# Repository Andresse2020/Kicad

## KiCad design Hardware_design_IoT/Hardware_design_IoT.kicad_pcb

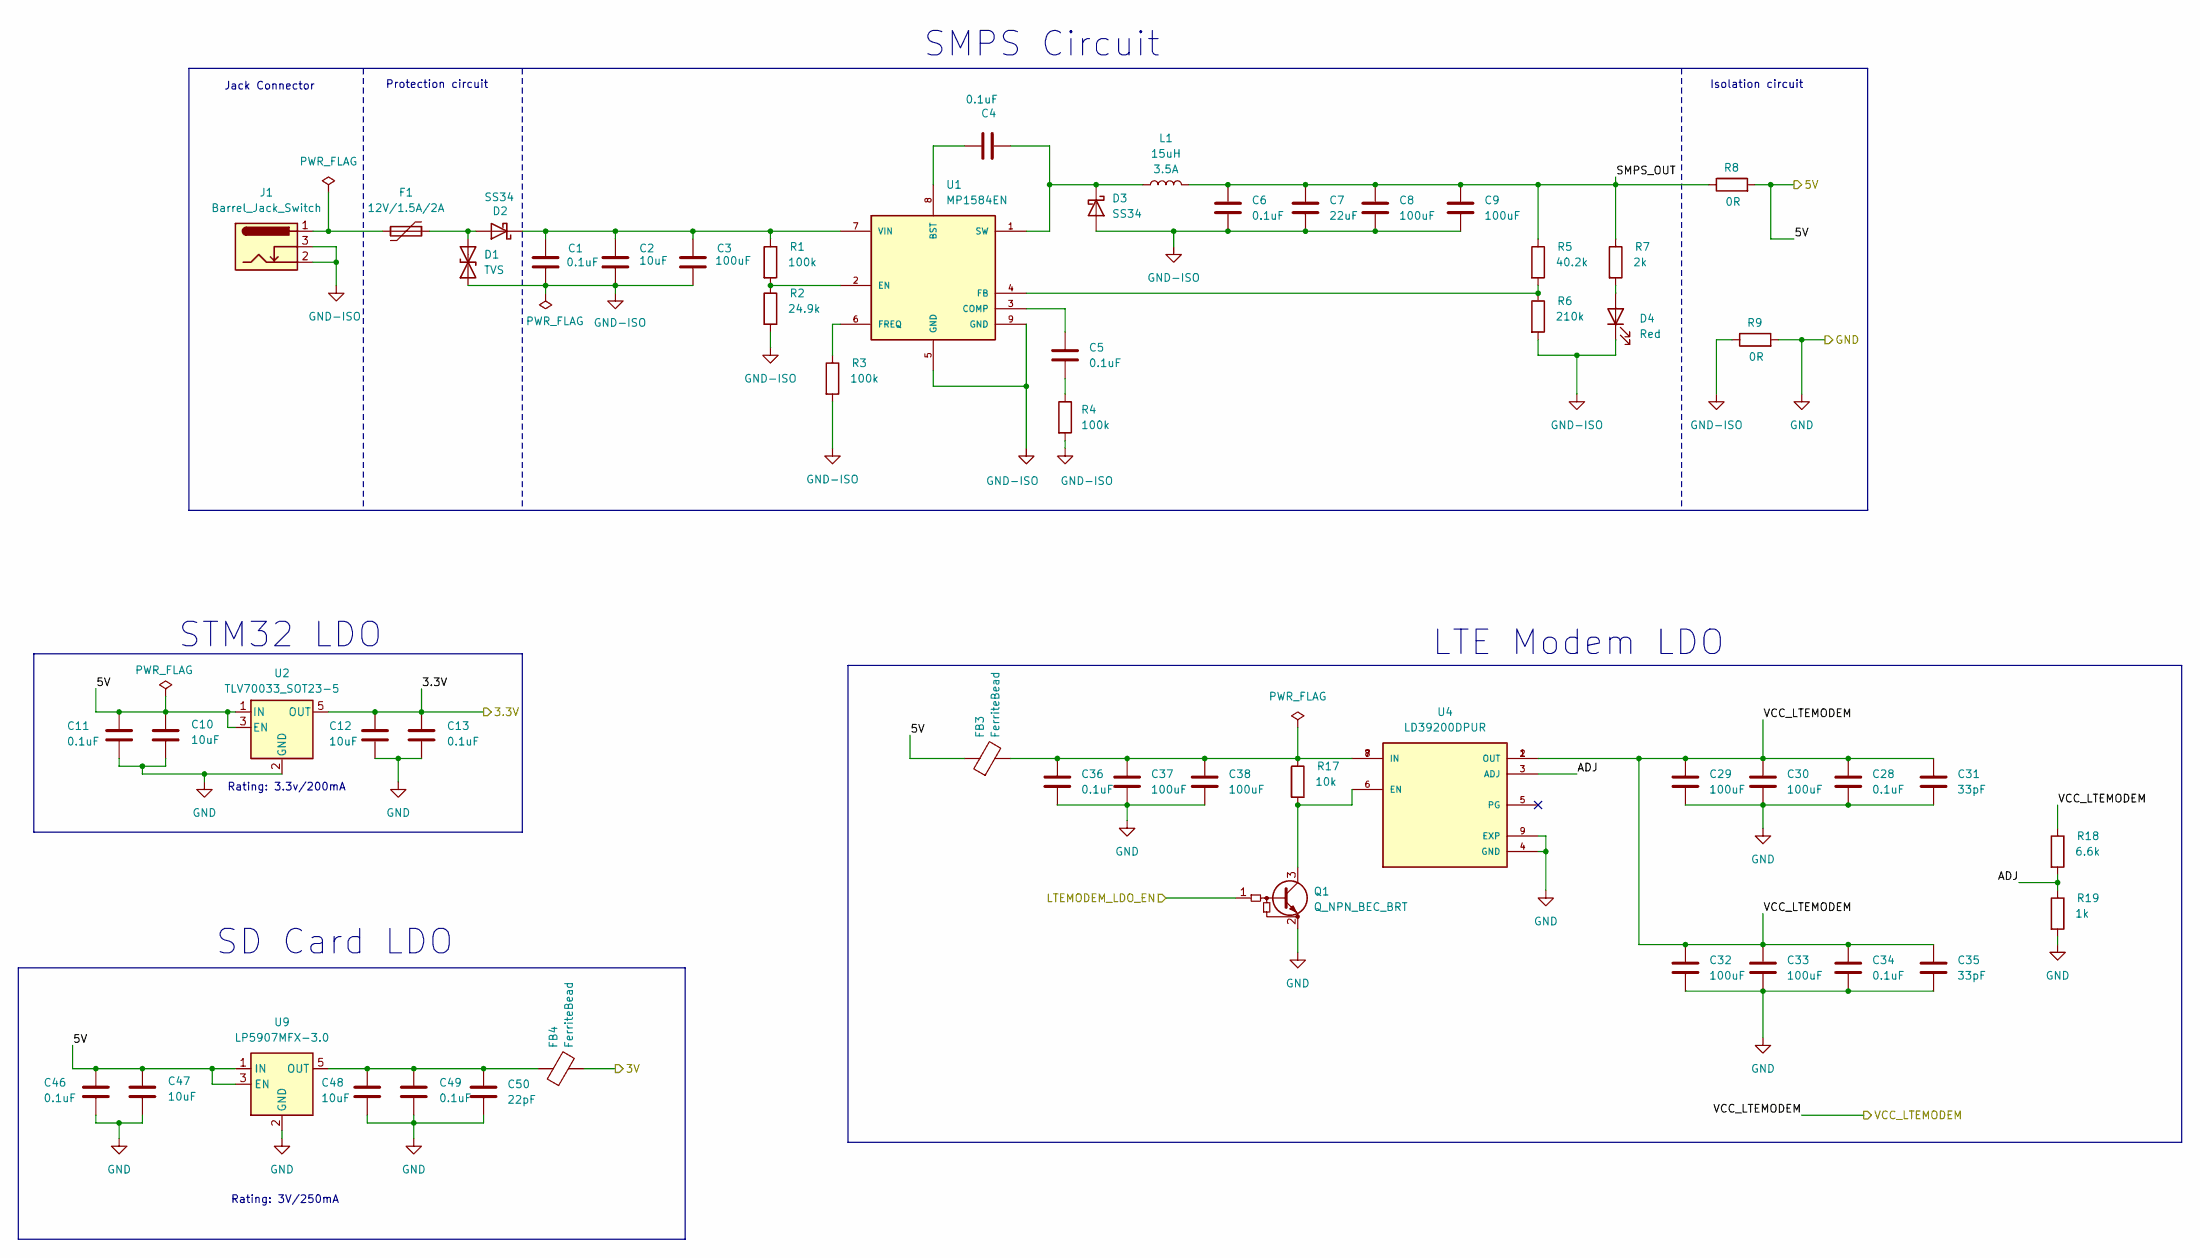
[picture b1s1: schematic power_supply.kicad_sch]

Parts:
C1, C4, C5, C6, C28, C34, C36: 0.1uF; C_0603_1608Metric_Pad1.08x0.95mm_HandSolder
C2: 10uF; C_0603_1608Metric_Pad1.08x0.95mm_HandSolder
C3, C8, C9, C29, C30, C32, C33, C37, C38: 100uF; C_1206_3216Metric_Pad1.33x1.80mm_HandSolder
C7: 22uF; C_0603_1608Metric_Pad1.08x0.95mm_HandSolder
C10, C12, C47, C48: 10uF; C_0603_1608Metric_Pad1.08x0.95mm_HandSolder; Voltage 1kV; Tolerance 100%
C11, C13, C46, C49: 0.1uF; C_0603_1608Metric_Pad1.08x0.95mm_HandSolder; Voltage 1kV; Tolerance 100%
C31, C35: 33pF; C_0603_1608Metric_Pad1.08x0.95mm_HandSolder
C50: 22pF; C_0603_1608Metric_Pad1.08x0.95mm_HandSolder
D1: TVS; D_0805_2012Metric_Pad1.15x1.40mm_HandSolder
D2, D3: SS34; D_SMA
D4: Red; LED_0402_1005Metric
F1: 12V/1.5A/2A; Fuse_0805_2012Metric
FB3, FB4: FerriteBead; BEADC2012X105N
J1: Barrel_Jack_Switch; BarrelJack_CLIFF_FC681465S_SMT_Horizontal
L1: 15uH; L_6.3x6.3_H3
Q1: Q_NPN_BEC_BRT; SOT-23
R1, R3, R4: 100k; R_0603_1608Metric
R2: 24.9k; R_0603_1608Metric
R5: 40.2k; R_0603_1608Metric
R6: 210k; R_0603_1608Metric
R7: 2k; R_0603_1608Metric
R8, R9: 0R; R_0603_1608Metric
R17: 10k; R_0603_1608Metric
R18: 6.6k; R_0603_1608Metric
R19: 1k; R_0603_1608Metric
U1: MP1584EN; SOIC127P600X170-9N
U2: TLV70033_SOT23-5; SOT-23-5
U4: LD39200DPUR; SON80P400X400X100-9N; PARTREV 3
U9: LP5907MFX-3.0; SOT-23-5

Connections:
/3.3V: C12.1, C13.1, U2.5 (OUT); also elsewhere on the board
/3V: FB4.2; also elsewhere on the board
/LTEMODEM_LDO_EN: Q1.1 (B); also elsewhere on the board
/Power Supply/5V: C10.1, C11.1, C46.1, C47.1, FB3.1, R8.2, U2.1 (IN), U2.3 (EN), U9.1 (IN), U9.3 (EN)
/Power Supply/ADJ: R18.2, R19.1, U4.3 (ADJ)
/Power Supply/SMPS_OUT: C6.1, C7.1, C8.1, C9.1, L1.2, R5.1, R7.1, R8.1
/VCC_LTEMODEM: C28.1, C29.1, C30.1, C31.1, C32.1, C33.1, C34.1, C35.1, R18.1, U4.1 (OUT), U4.2 (OUT); also elsewhere on the board
GND: C10.2, C11.2, C12.2, C13.2, C28.2, C29.2, C30.2, C31.2, C32.2, C33.2, C34.2, C35.2, C36.2, C37.2, C38.2, C46.2, C47.2, C48.2, C49.2, C50.2, Q1.2 (E), R9.2, R19.2, U2.2 (GND), U4.4 (GND), U4.9 (EXP), U9.2 (GND); also elsewhere on the board
GND-ISO: C1.2, C2.2, C3.2, C6.2, C7.2, C8.2, C9.2, D1.1 (A1), D3.2 (A), D4.1 (K), J1.2, J1.3, R2.2, R3.2, R4.2, R6.2, R9.1, U1.5 (GND), U1.9 (GND)
unnamed: C5.2, R4.1
unnamed: C36.1, C37.1, C38.1, FB3.2, R17.1, U4.7 (IN), U4.8 (IN)
unnamed: D1.2 (A2), D2.2 (A), F1.1
unnamed: C1.1, C2.1, C3.1, D2.1 (K), R1.1, U1.7 (VIN)
unnamed: C4.2, D3.1 (K), L1.1, U1.1 (SW)
unnamed: D4.2 (A), R7.2
unnamed: F1.2, J1.1
unnamed: Q1.3 (C), R17.2, U4.6 (EN)
unnamed: C4.1, U1.8 (BST)
unnamed: C5.1, U1.3 (COMP)
unnamed: R1.2, R2.1, U1.2 (EN)
unnamed: R5.2, R6.1, U1.4 (FB)
unnamed: R3.1, U1.6 (FREQ)
unnamed: C48.1, C49.1, C50.1, FB4.1, U9.5 (OUT)

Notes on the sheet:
Protection circuit
LTE Modem LDO
Jack Connector
Isolation circuit
Rating: 3V/250mA
Rating: 3.3v/200mA
SD Card LDO
STM32 LDO
SMPS Circuit

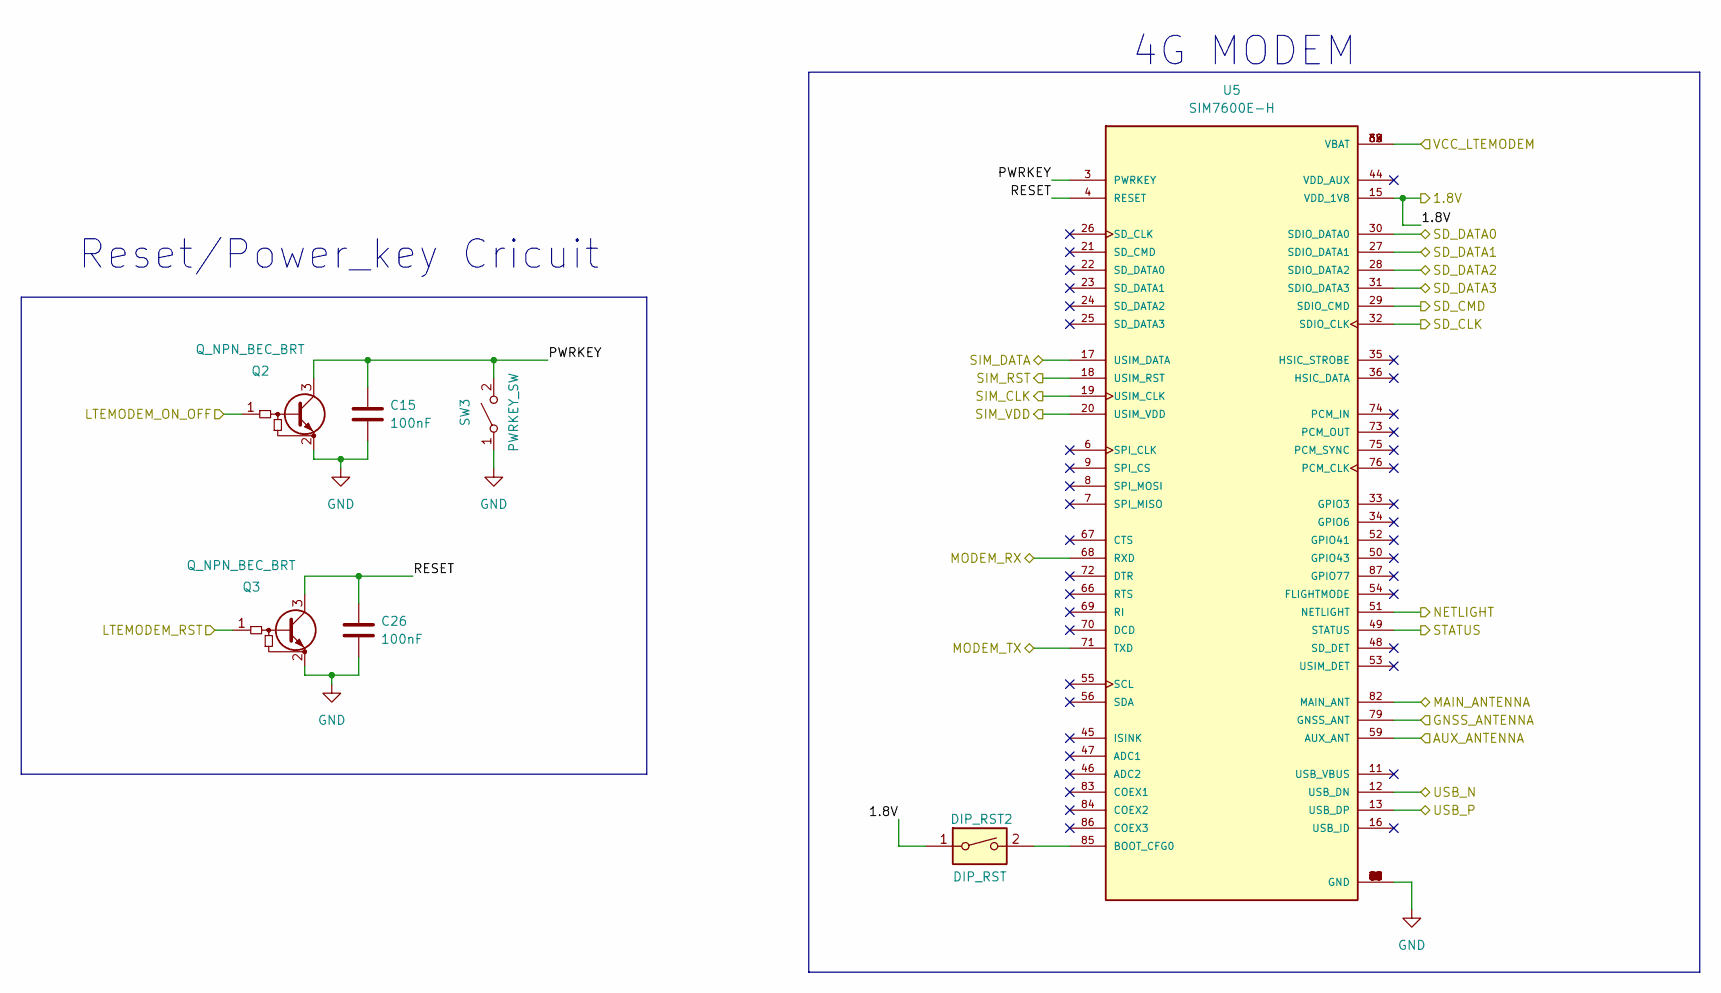
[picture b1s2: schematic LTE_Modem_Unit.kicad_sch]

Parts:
C15, C26: 100nF; C_0603_1608Metric_Pad1.08x0.95mm_HandSolder
DIP_RST2: DIP_RST; SW_DIP_SPSTx01_Slide_6.7x4.1mm_W6.73mm_P2.54mm_LowProfile_J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
Q2, Q3: Q_NPN_BEC_BRT; SOT-23
SW3: PWRKEY_SW; SW_Tactile_SPST_NO_Straight_CK_PTS636Sx25SMTRLFS
U5: SIM7600E-H; IC_SIM7600E-H; M_PART_NUMBER SIM7600E-H

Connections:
/1.8V: DIP_RST2.1, U5.15 (VDD_1V8); also elsewhere on the board
/AUX_ANTENNA: U5.59 (AUX_ANT); also elsewhere on the board
/GNSS_ANTENNA: U5.79 (GNSS_ANT); also elsewhere on the board
/LTE Modem Unit/PWRKEY: C15.1, Q2.3 (C), SW3.2 (B), U5.3 (PWRKEY)
/LTE Modem Unit/RESET: C26.1, Q3.3 (C), U5.4 (RESET)
/LTEMODEM_ON_OFF: Q2.1 (B); also elsewhere on the board
/LTEMODEM_RST: Q3.1 (B); also elsewhere on the board
/MAIN_ANTENNA: U5.82 (MAIN_ANT); also elsewhere on the board
/MODEM_RX: U5.68 (RXD); also elsewhere on the board
/MODEM_TX: U5.71 (TXD); also elsewhere on the board
/NETLIGHT: U5.51 (NETLIGHT); also elsewhere on the board
/SD_CLK: U5.32 (SDIO_CLK); also elsewhere on the board
/SD_CMD: U5.29 (SDIO_CMD); also elsewhere on the board
/SD_DATA0: U5.30 (SDIO_DATA0); also elsewhere on the board
/SD_DATA1: U5.27 (SDIO_DATA1); also elsewhere on the board
/SD_DATA2: U5.28 (SDIO_DATA2); also elsewhere on the board
/SD_DATA3: U5.31 (SDIO_DATA3); also elsewhere on the board
/SIM_CLK: U5.19 (USIM_CLK); also elsewhere on the board
/SIM_DATA: U5.17 (USIM_DATA); also elsewhere on the board
/SIM_RST: U5.18 (USIM_RST); also elsewhere on the board
/SIM_VDD: U5.20 (USIM_VDD); also elsewhere on the board
/STATUS: U5.49 (STATUS); also elsewhere on the board
/USB_N: U5.12 (USB_DN); also elsewhere on the board
/USB_P: U5.13 (USB_DP); also elsewhere on the board
/VCC_LTEMODEM: U5.38 (VBAT), U5.39 (VBAT), U5.62 (VBAT), U5.63 (VBAT); also elsewhere on the board
GND: C15.2, C26.2, Q2.2 (E), Q3.2 (E), SW3.1 (A), U5.1 (GND), U5.2 (GND), U5.5 (GND), U5.10 (GND), U5.14 (GND), U5.37 (GND), U5.40 (GND), U5.41 (GND), U5.43 (GND), U5.57 (GND), U5.58 (GND), U5.60 (GND), U5.61 (GND), U5.64 (GND), U5.65 (GND), U5.77 (GND), U5.78 (GND), U5.80 (GND), U5.81 (GND); also elsewhere on the board
unnamed: DIP_RST2.2, U5.85 (BOOT_CFG0)

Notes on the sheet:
4G MODEM
Reset/Power_key Cricuit

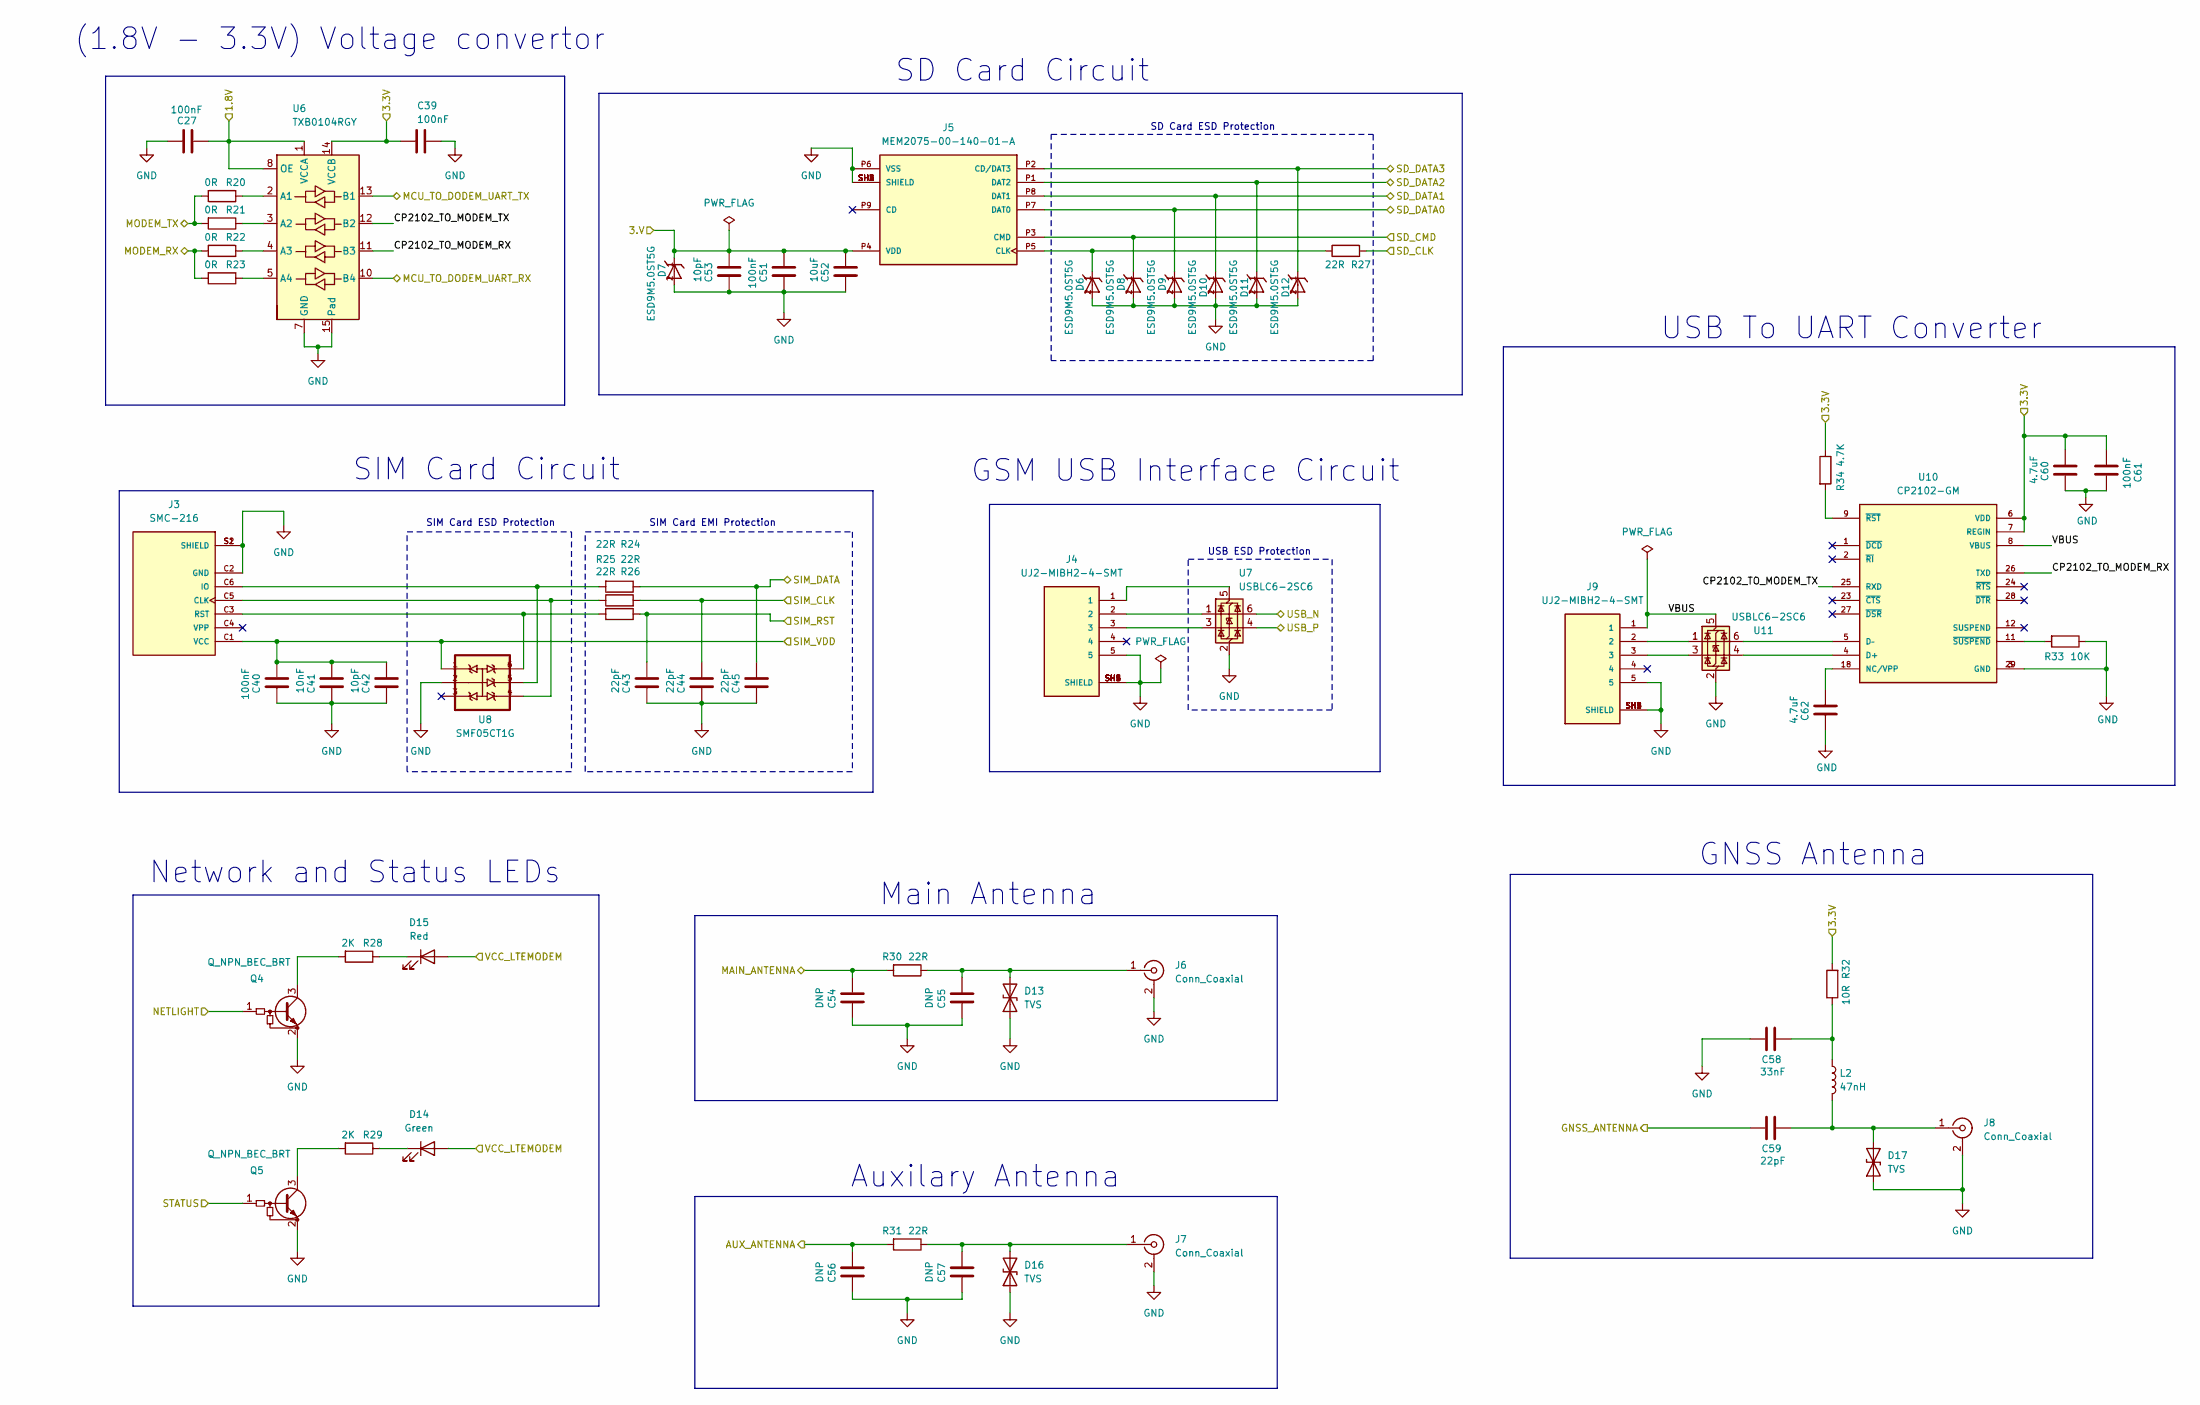
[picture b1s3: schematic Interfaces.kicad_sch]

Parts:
C27, C39, C40, C51, C61: 100nF; C_0603_1608Metric_Pad1.08x0.95mm_HandSolder
C41: 10nF; C_0603_1608Metric_Pad1.08x0.95mm_HandSolder
C42, C53: 10pF; C_0603_1608Metric_Pad1.08x0.95mm_HandSolder
C43, C44, C45: 22pF; C_0603_1608Metric_Pad1.08x0.95mm_HandSolder
C52: 10uF; C_0603_1608Metric_Pad1.08x0.95mm_HandSolder
C54, C55, C56, C57: DNP; C_0402_1005Metric_Pad0.74x0.62mm_HandSolder
C58: 33nF; C_0402_1005Metric_Pad0.74x0.62mm_HandSolder
C59: 22pF; C_0402_1005Metric_Pad0.74x0.62mm_HandSolder
C60, C62: 4.7uF; C_0603_1608Metric_Pad1.08x0.95mm_HandSolder
D6, D7, D8, D9, D10, D11, D12: ESD9M5.0ST5G; SODFL1060X40N
D13, D16, D17: TVS; D_0603_1608Metric
D14: Green; LED_0603_1608Metric
D15: Red; LED_0603_1608Metric
J3: SMC-216; XUNPU_SMC-216; PARTREV B
J4, J9: UJ2-MIBH2-4-SMT; CUI_UJ2-MIBH2-4-SMT; PART_REV 1.0
J5: MEM2075-00-140-01-A; GCT_MEM2075-00-140-01-A; PARTREV A
J6, J7, J8: Conn_Coaxial; U.FL_Molex_MCRF_73412-0110_Vertical
L2: 47nH; L_0402_1005Metric
Q4, Q5: Q_NPN_BEC_BRT; SOT-23
R20, R21, R22, R23: 0R; R_0603_1608Metric
R24, R25, R26, R27: 22R; R_0603_1608Metric
R28, R29: 2K; R_0603_1608Metric
R30, R31: 22R; R_0402_1005Metric
R32: 10R; R_0402_1005Metric
R33: 10K; R_0402_1005Metric
R34: 4.7K; R_0402_1005Metric
U6: TXB0104RGY; Texas_S-PVQFN-N14
U7, U11: USBLC6-2SC6; SOT-23-6
U8: SMF05CT1G; SOT65P210X110-6N
U10: CP2102-GM; QFN50P500X500X100-29N; PARTREV 1.8

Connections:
/1.8V: C27.2, U6.1 (VCCA), U6.8 (OE); also elsewhere on the board
/3.3V: C39.2, C60.2, C61.2, R32.2, R34.1, U6.14 (VCCB), U10.6 (VDD), U10.7 (REGIN); also elsewhere on the board
/3V: C51.2, C52.2, C53.2, D7.1, J5.P4 (VDD); also elsewhere on the board
/AUX_ANTENNA: C56.2, R31.2; also elsewhere on the board
/GNSS_ANTENNA: C59.2; also elsewhere on the board
/Interfaces/CP2102_TO_MODEM_RX: U6.11 (B3), U10.26 (TXD)
/Interfaces/CP2102_TO_MODEM_TX: U6.12 (B2), U10.25 (RXD)
/Interfaces/VBUS: J9.1, U10.8 (VBUS), U11.5 (VBUS)
/MAIN_ANTENNA: C54.2, R30.2; also elsewhere on the board
/MCU_TO_MODEM_UART_RX: U6.10 (B4); also elsewhere on the board
/MCU_TO_MODEM_UART_TX: U6.13 (B1); also elsewhere on the board
/MODEM_RX: R22.2, R23.2; also elsewhere on the board
/MODEM_TX: R20.2, R21.2; also elsewhere on the board
/NETLIGHT: Q4.1 (B); also elsewhere on the board
/SD_CLK: R27.2; also elsewhere on the board
/SD_CMD: D8.1, J5.P3 (CMD); also elsewhere on the board
/SD_DATA0: D9.1, J5.P7 (DAT0); also elsewhere on the board
/SD_DATA1: D10.1, J5.P8 (DAT1); also elsewhere on the board
/SD_DATA2: D11.1, J5.P1 (DAT2); also elsewhere on the board
/SD_DATA3: D12.1, J5.P2 (CD/DAT3); also elsewhere on the board
/SIM_CLK: C44.2, R25.2; also elsewhere on the board
/SIM_DATA: C45.2, R24.1; also elsewhere on the board
/SIM_RST: C43.2, R26.1; also elsewhere on the board
/SIM_VDD: C40.2, C41.2, C42.2, J3.C1 (VCC), U8.1; also elsewhere on the board
/STATUS: Q5.1 (B); also elsewhere on the board
/USB_N: U7.6 (I/O1); also elsewhere on the board
/USB_P: U7.4 (I/O2); also elsewhere on the board
/VCC_LTEMODEM: D14.2 (A), D15.2 (A); also elsewhere on the board
GND: C27.1, C39.1, C40.1, C41.1, C42.1, C43.1, C44.1, C45.1, C51.1, C52.1, C53.1, C54.1, C55.1, C56.1, C57.1, C58.2, C60.1, C61.1, C62.1, D6.2, D7.2, D8.2, D9.2, D10.2, D11.2, D12.2, D13.1 (A1), D16.1 (A1), D17.1 (A1), J3.C2 (GND), J3.S1 (SHIELD), J3.S2 (SHIELD), J4.5, J4.SH1 (SHIELD), J4.SH2 (SHIELD), J4.SH3 (SHIELD), J4.SH4 (SHIELD), J4.SH5 (SHIELD), J5.P6 (VSS), J5.SH1 (SHIELD), J5.SH2 (SHIELD), J5.SH3 (SHIELD), J5.SH4 (SHIELD), J6.2 (Ext), J7.2 (Ext), J8.2 (Ext), J9.5, J9.SH1 (SHIELD), J9.SH2 (SHIELD), J9.SH3 (SHIELD), J9.SH4 (SHIELD), J9.SH5 (SHIELD), Q4.2 (E), Q5.2 (E), R33.1, U6.7 (GND), U6.15 (Pad), U7.2 (GND), U8.2, U10.3 (GND), U10.29 (GND), U11.2 (GND); also elsewhere on the board
unnamed: C58.1, L2.1, R32.1
unnamed: C55.2, D13.2 (A2), J6.1 (In), R30.1
unnamed: D14.1 (K), R29.1
unnamed: D15.1 (K), R28.1
unnamed: C57.2, D16.2 (A2), J7.1 (In), R31.1
unnamed: C59.1, D17.2 (A2), J8.1 (In), L2.2
unnamed: J3.C5 (CLK), R25.1, U8.4
unnamed: J3.C6 (IO), R24.2, U8.5
unnamed: J3.C3 (RST), R26.2, U8.6
unnamed: J4.2, U7.1 (I/O1)
unnamed: J4.3, U7.3 (I/O2)
unnamed: D6.1, J5.P5 (CLK), R27.1
unnamed: J9.2, U11.1 (I/O1)
unnamed: J9.3, U11.3 (I/O2)
unnamed: Q4.3 (C), R28.2
unnamed: Q5.3 (C), R29.2
unnamed: R20.1, U6.2 (A1)
unnamed: R21.1, U6.3 (A2)
unnamed: R22.1, U6.4 (A3)
unnamed: R23.1, U6.5 (A4)
unnamed: J4.1, U7.5 (VBUS)
unnamed: U10.4 (D+), U11.4 (I/O2)
unnamed: U10.5 (D–), U11.6 (I/O1)
unnamed: C62.2, U10.18 (NC/VPP)
unnamed: R34.2, U10.9 (~RST)
unnamed: R33.2, U10.11 (~SUSPEND)

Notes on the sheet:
(1.8V - 3.3V) Voltage convertor
GNSS Antenna
SIM Card ESD Protection
SD Card Circuit
GSM USB Interface Circuit
USB To UART Converter
USB ESD Protection
Main Antenna
SIM Card EMI Protection
SD Card ESD Protection
SIM Card Circuit
Auxilary Antenna
Network and Status LEDs

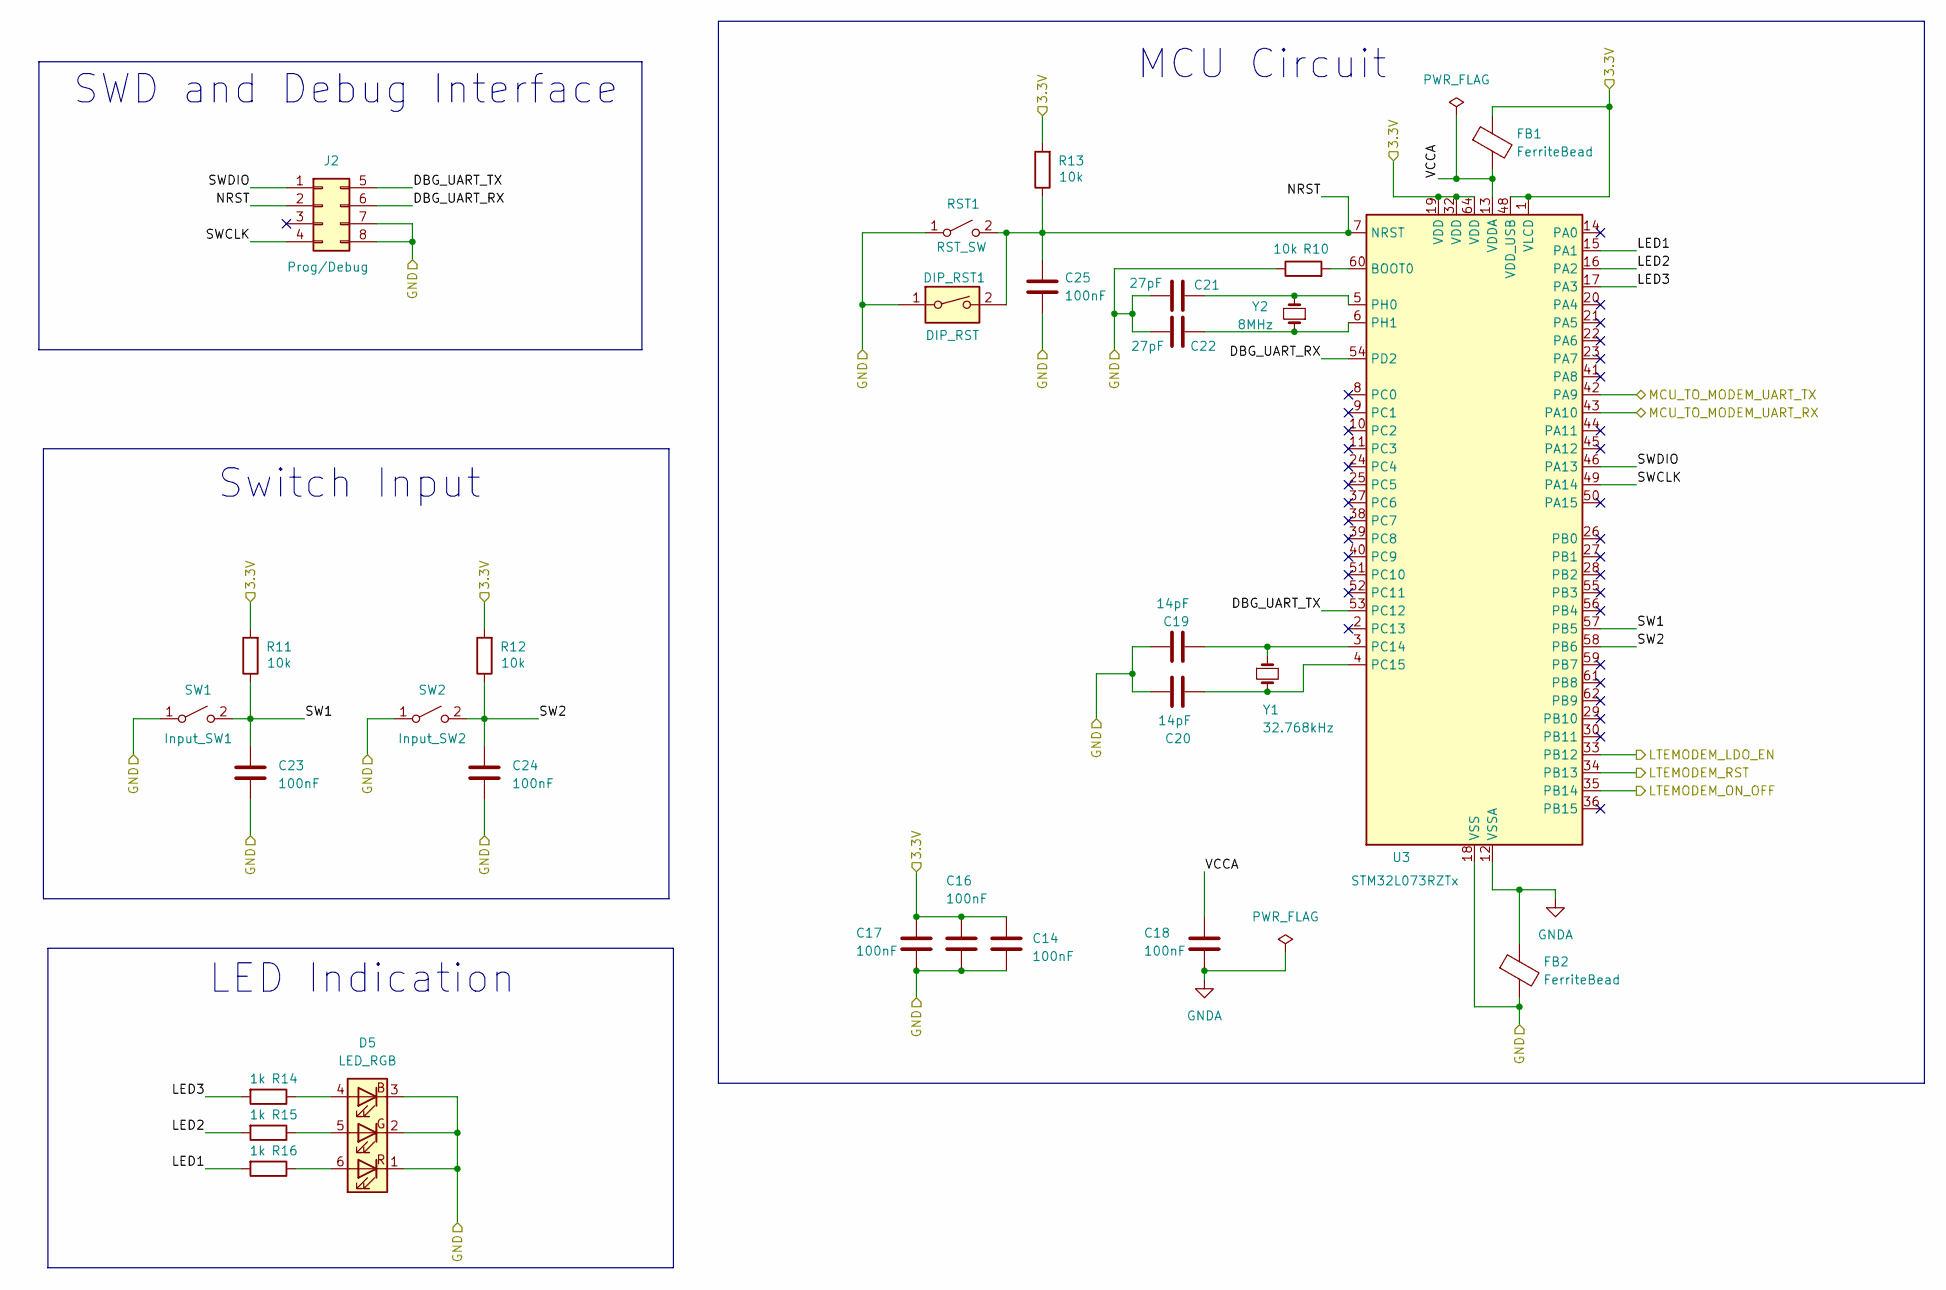
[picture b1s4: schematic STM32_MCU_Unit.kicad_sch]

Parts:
C14, C16, C17, C18, C23, C24, C25: 100nF; C_0603_1608Metric_Pad1.08x0.95mm_HandSolder
C19, C20: 14pF; C_0603_1608Metric_Pad1.08x0.95mm_HandSolder
C21, C22: 27pF; C_0603_1608Metric_Pad1.08x0.95mm_HandSolder
D5: LED_RGB; ASMT-YTC7-0AA02
DIP_RST1: DIP_RST; SW_DIP_SPSTx01_Slide_6.7x4.1mm_W6.73mm_P2.54mm_LowProfile_J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
FB1, FB2: FerriteBead; BEADC2012X105N
J2: Prog/Debug; PinHeader_2x04_P2.54mm_Vertical
R10, R11, R12, R13: 10k; R_0603_1608Metric
R14, R15, R16: 1k; R_0603_1608Metric
RST1: RST_SW; SW_Tactile_SPST_NO_Straight_CK_PTS636Sx25SMTRLFS
SW1: Input_SW1; SW_Tactile_SPST_NO_Straight_CK_PTS636Sx25SMTRLFS
SW2: Input_SW2; SW_Tactile_SPST_NO_Straight_CK_PTS636Sx25SMTRLFS
U3: STM32L073RZTx; LQFP-64_10x10mm_P0.5mm
Y1: 32.768kHz; Crystal_SMD_0603-2Pin_6.0x3.5mm
Y2: 8MHz; Crystal_SMD_5032-2Pin_5.0x3.2mm

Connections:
/3.3V: C14.1, C16.1, C17.1, FB1.1, R11.2, R12.2, R13.2, U3.1 (VLCD), U3.19 (VDD), U3.32 (VDD), U3.48 (VDD_USB), U3.64 (VDD); also elsewhere on the board
/LTEMODEM_LDO_EN: U3.33 (PB12); also elsewhere on the board
/LTEMODEM_ON_OFF: U3.35 (PB14); also elsewhere on the board
/LTEMODEM_RST: U3.34 (PB13); also elsewhere on the board
/MCU_TO_MODEM_UART_RX: U3.42 (PA9); also elsewhere on the board
/MCU_TO_MODEM_UART_TX: U3.43 (PA10); also elsewhere on the board
/STM32 MCU Unit/DBG_UART_RX: J2.6, U3.54 (PD2)
/STM32 MCU Unit/DBG_UART_TX: J2.5, U3.53 (PC12)
/STM32 MCU Unit/LED1: R16.2, U3.15 (PA1)
/STM32 MCU Unit/LED2: R15.2, U3.16 (PA2)
/STM32 MCU Unit/LED3: R14.2, U3.17 (PA3)
/STM32 MCU Unit/NRST: C25.1, DIP_RST1.2, J2.2, R13.1, RST1.2 (B), U3.7 (NRST)
/STM32 MCU Unit/SW1: C23.1, R11.1, SW1.2 (B), U3.57 (PB5)
/STM32 MCU Unit/SW2: C24.1, R12.1, SW2.2 (B), U3.58 (PB6)
/STM32 MCU Unit/SWCLK: J2.4, U3.49 (PA14)
/STM32 MCU Unit/SWDIO: J2.1, U3.46 (PA13)
/STM32 MCU Unit/VCCA: C18.1, FB1.2, U3.13 (VDDA)
GND: C14.2, C16.2, C17.2, C19.1, C20.1, C21.1, C22.1, C23.2, C24.2, C25.2, D5.1 (RK), D5.2 (GK), D5.3 (BK), DIP_RST1.1, FB2.2, J2.7, J2.8, R10.1, RST1.1 (A), SW1.1 (A), SW2.1 (A), U3.18 (VSS), U3.31 (VSS), U3.47 (VSS), U3.63 (VSS); also elsewhere on the board
GNDA: C18.2, FB2.1, U3.12 (VSSA)
unnamed: D5.4 (BA), R14.1
unnamed: D5.5 (GA), R15.1
unnamed: D5.6 (RA), R16.1
unnamed: R10.2, U3.60 (BOOT0)
unnamed: C19.2, U3.3 (PC14), Y1.1
unnamed: C20.2, U3.4 (PC15), Y1.2
unnamed: C21.2, U3.5 (PH0), Y2.2
unnamed: C22.2, U3.6 (PH1), Y2.1

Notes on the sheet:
Switch Input
LED Indication
MCU Circuit
SWD and Debug Interface

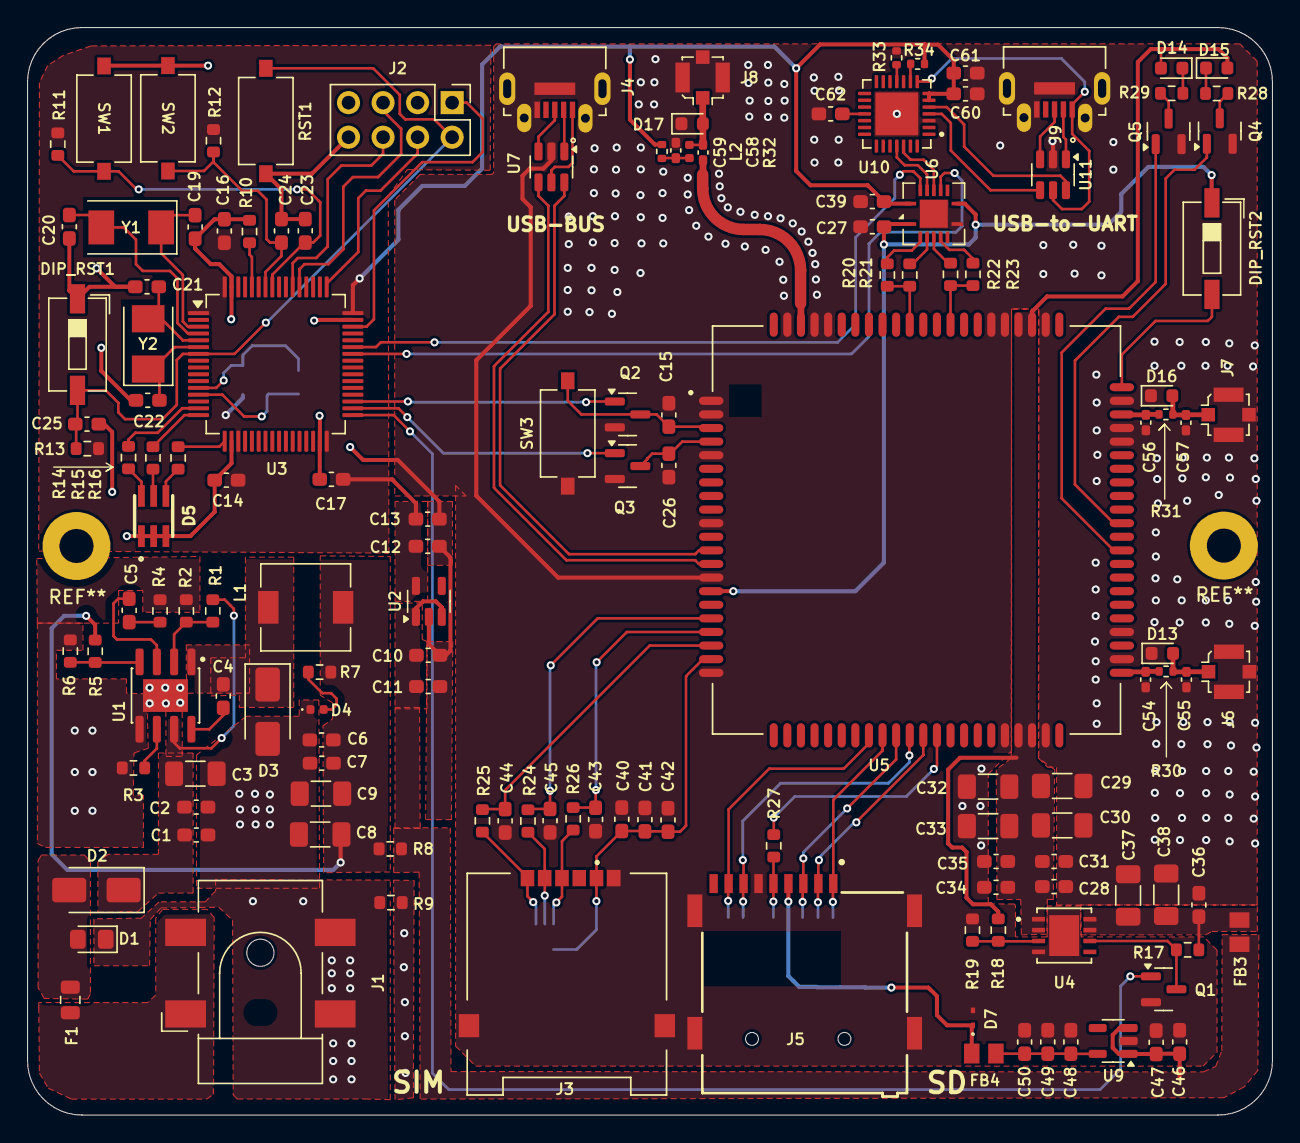
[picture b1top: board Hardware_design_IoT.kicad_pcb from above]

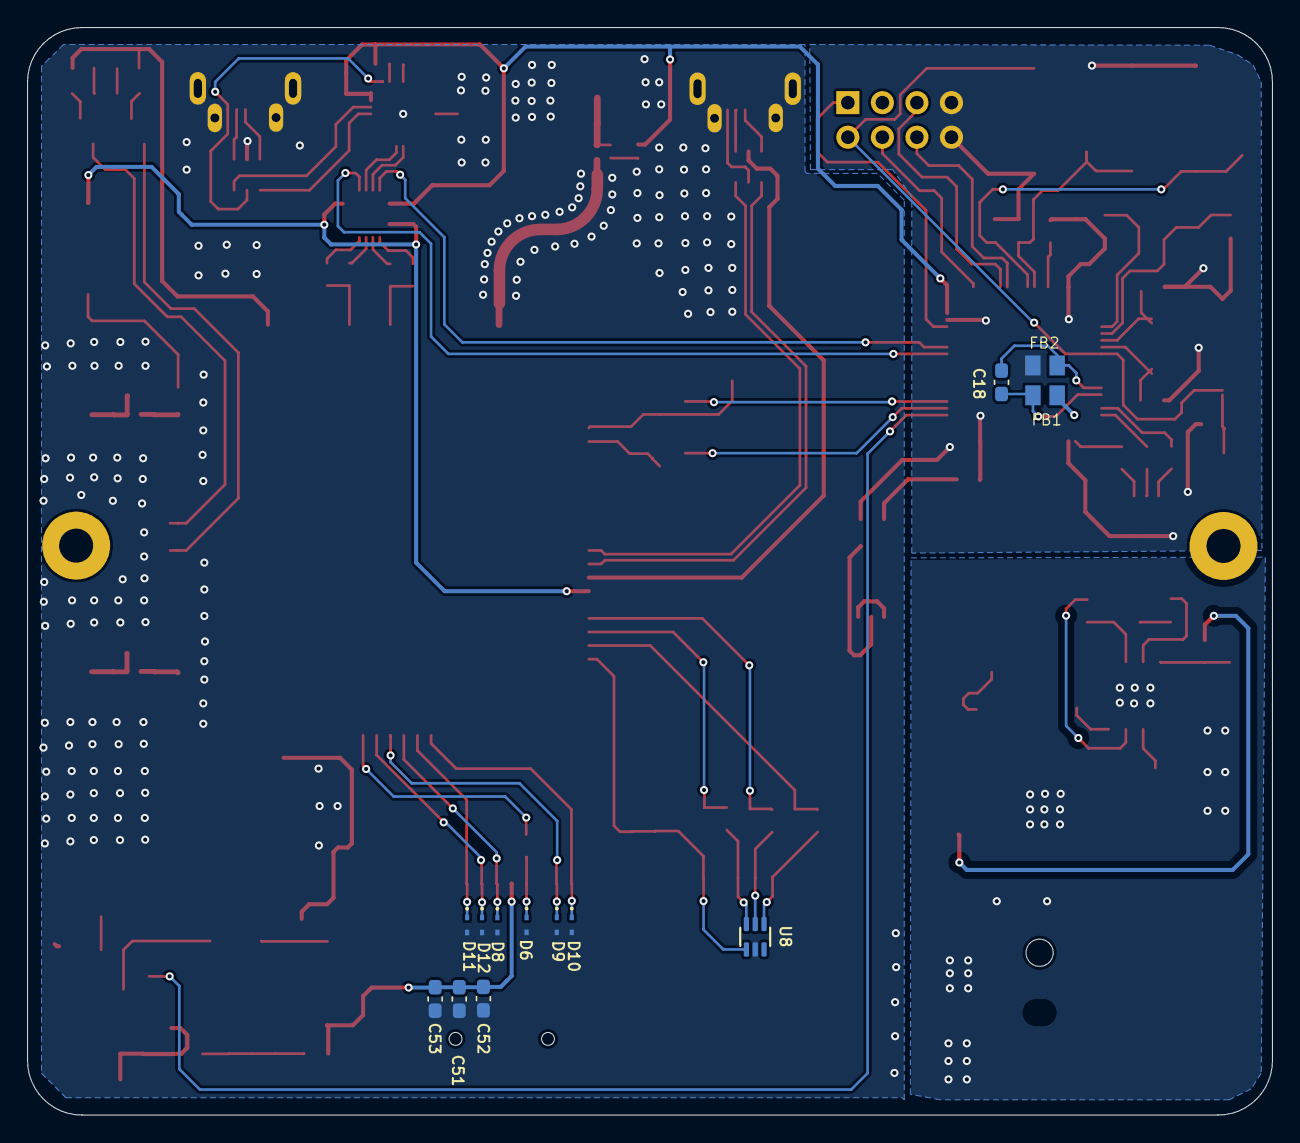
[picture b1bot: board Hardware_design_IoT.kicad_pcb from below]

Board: 2 copper layers, 91.6 x 80.0 mm, 153 parts (13 on the bottom side), 99 nets.
